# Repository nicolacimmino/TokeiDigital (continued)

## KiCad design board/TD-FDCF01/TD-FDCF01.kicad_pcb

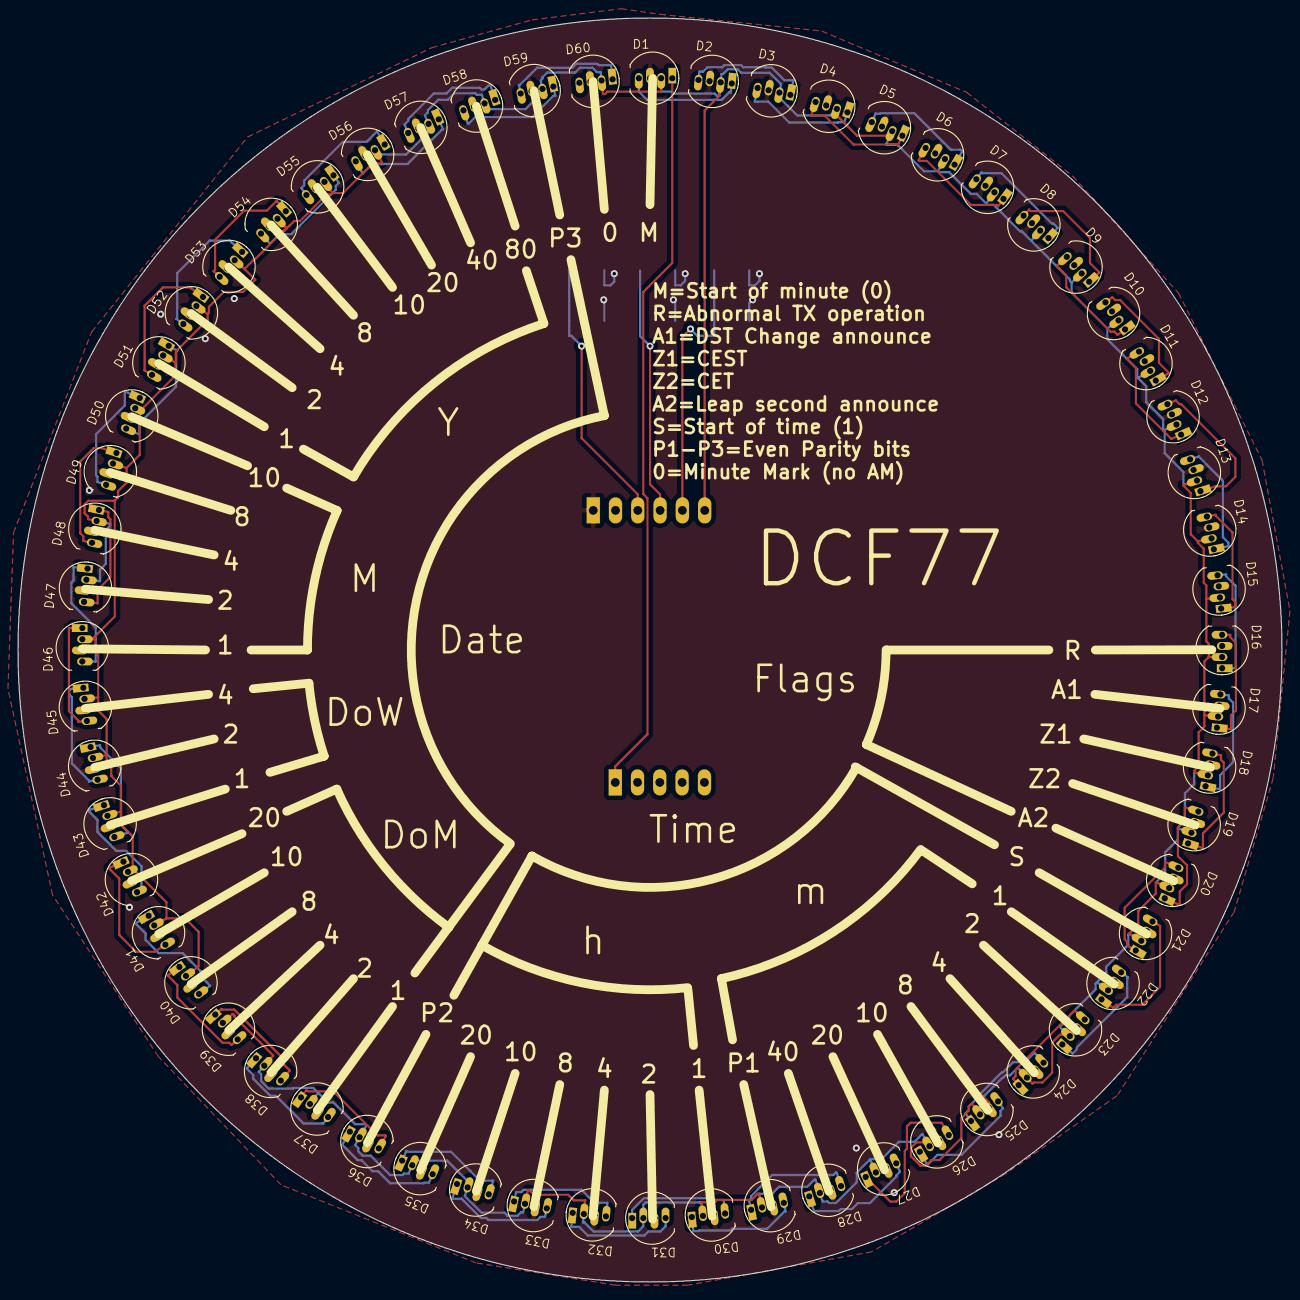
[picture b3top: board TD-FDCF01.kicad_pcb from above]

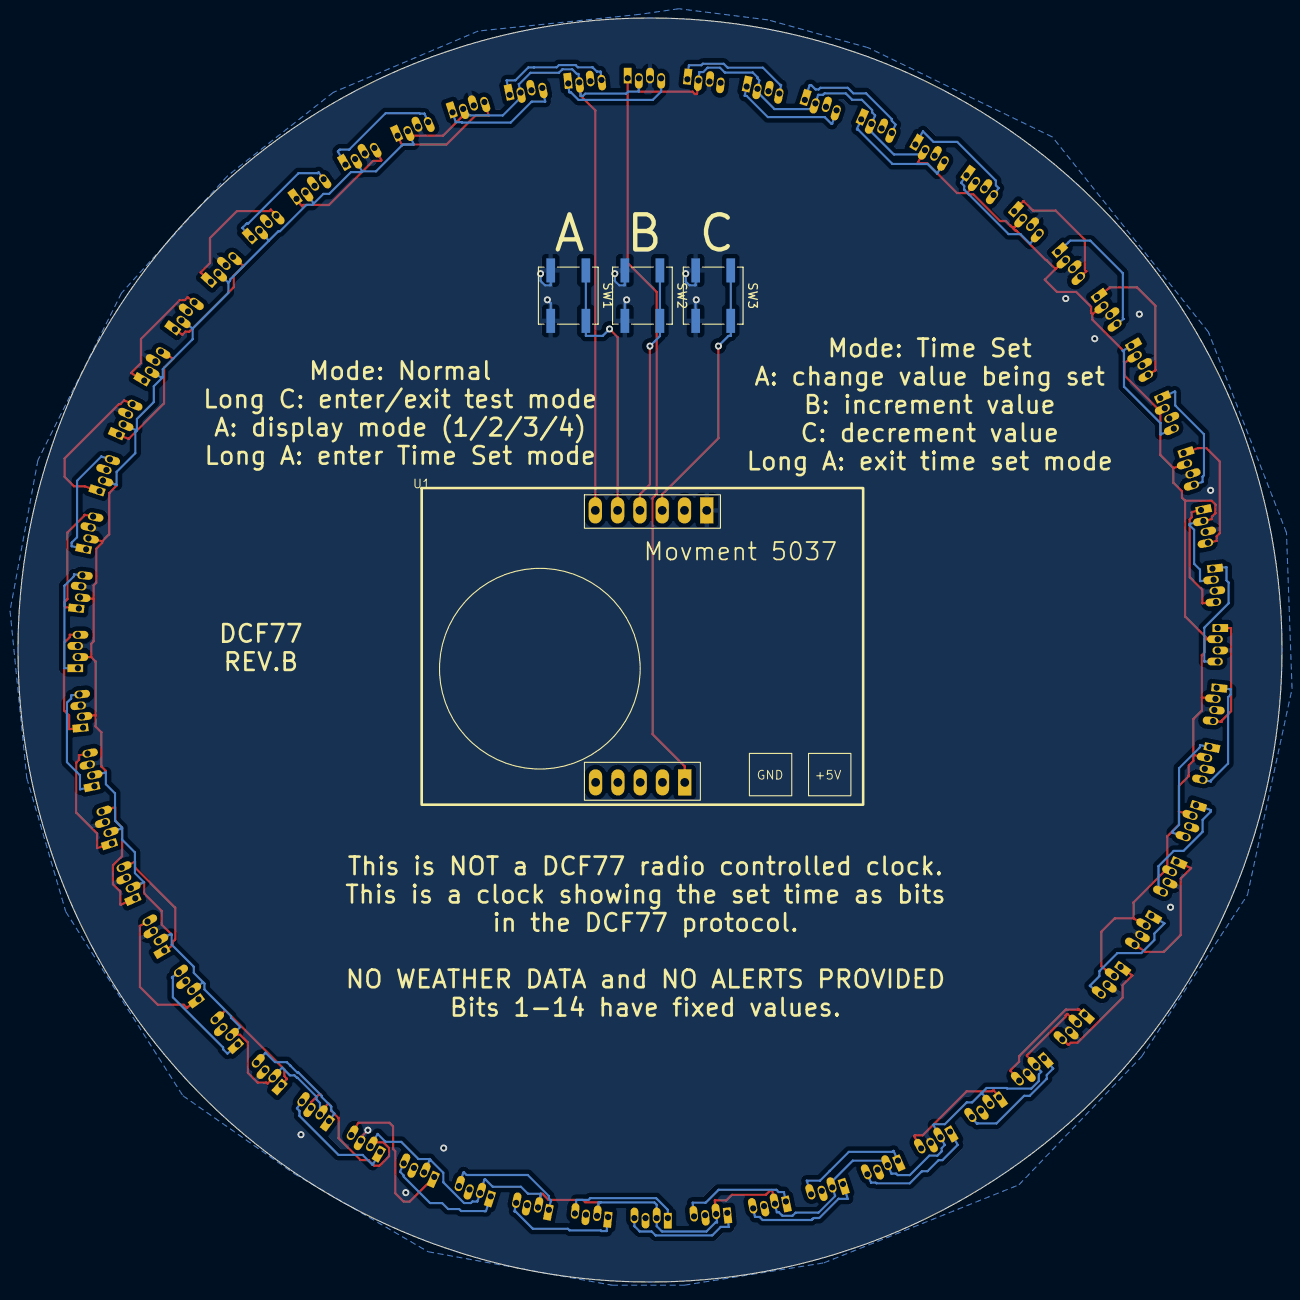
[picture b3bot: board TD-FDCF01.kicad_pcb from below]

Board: 2 copper layers, 144.0 x 144.0 mm, 64 parts (4 on the bottom side), 65 nets.

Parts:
D1, D2, D3, D4, D5, D6, D7, D8, D9, D10, D11, D12, D13, D14, D15, D16, D17, D18, D19, D20, D21, D22, D23, D24, D25, D26, D27, D28, D29, D30, D31, D32, D33, D34, D35, D36, D37, D38, D39, D40, D41, D42, D43, D44, D45, D46, D47, D48, D49, D50, D51, D52, D53, D54, D55, D56, D57, D58, D59, D60: WS2812-5MM
SW1, SW2, SW3: SW_Push; Tactile SW SMD
U1: Movement5037 TH

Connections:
+5V: D1.2 (Vcc), D2.2 (Vcc), D3.2 (Vcc), D4.2 (Vcc), D5.2 (Vcc), D6.2 (Vcc), D7.2 (Vcc), D8.2 (Vcc), D9.2 (Vcc), D10.2 (Vcc), D11.2 (Vcc), D12.2 (Vcc), D13.2 (Vcc), D14.2 (Vcc), D15.2 (Vcc), D16.2 (Vcc), D17.2 (Vcc), D18.2 (Vcc), D19.2 (Vcc), D20.2 (Vcc), D21.2 (Vcc), D22.2 (Vcc), D23.2 (Vcc), D24.2 (Vcc), D25.2 (Vcc), D26.2 (Vcc), D27.2 (Vcc), D28.2 (Vcc), D29.2 (Vcc), D30.2 (Vcc), D31.2 (Vcc), D32.2 (Vcc), D33.2 (Vcc), D34.2 (Vcc), D35.2 (Vcc), D36.2 (Vcc), D37.2 (Vcc), D38.2 (Vcc), D39.2 (Vcc), D40.2 (Vcc), D41.2 (Vcc), D42.2 (Vcc), D43.2 (Vcc), D44.2 (Vcc), D45.2 (Vcc), D46.2 (Vcc), D47.2 (Vcc), D48.2 (Vcc), D49.2 (Vcc), D50.2 (Vcc), D51.2 (Vcc), D52.2 (Vcc), D53.2 (Vcc), D54.2 (Vcc), D55.2 (Vcc), D56.2 (Vcc), D57.2 (Vcc), D58.2 (Vcc), D59.2 (Vcc), D60.2 (Vcc), U1.6 (+5)
/LEDD: D1.1 (DIn), U1.7 (WS2812D)
/LedA/LEDD_CONT: D30.4 (DOut), D31.1 (DIn)
GND: D1.3 (GND), D2.3 (GND), D3.3 (GND), D4.3 (GND), D5.3 (GND), D6.3 (GND), D7.3 (GND), D8.3 (GND), D9.3 (GND), D10.3 (GND), D11.3 (GND), D12.3 (GND), D13.3 (GND), D14.3 (GND), D15.3 (GND), D16.3 (GND), D17.3 (GND), D18.3 (GND), D19.3 (GND), D20.3 (GND), D21.3 (GND), D22.3 (GND), D23.3 (GND), D24.3 (GND), D25.3 (GND), D26.3 (GND), D27.3 (GND), D28.3 (GND), D29.3 (GND), D30.3 (GND), D31.3 (GND), D32.3 (GND), D33.3 (GND), D34.3 (GND), D35.3 (GND), D36.3 (GND), D37.3 (GND), D38.3 (GND), D39.3 (GND), D40.3 (GND), D41.3 (GND), D42.3 (GND), D43.3 (GND), D44.3 (GND), D45.3 (GND), D46.3 (GND), D47.3 (GND), D48.3 (GND), D49.3 (GND), D50.3 (GND), D51.3 (GND), D52.3 (GND), D53.3 (GND), D54.3 (GND), D55.3 (GND), D56.3 (GND), D57.3 (GND), D58.3 (GND), D59.3 (GND), D60.3 (GND), SW1.2, SW2.2, SW3.2, U1.1 (GND)
unnamed: D1.4 (DOut), D2.1 (DIn)
unnamed: D2.4 (DOut), D3.1 (DIn)
unnamed: D3.4 (DOut), D4.1 (DIn)
unnamed: D4.4 (DOut), D5.1 (DIn)
unnamed: D5.4 (DOut), D6.1 (DIn)
unnamed: D6.4 (DOut), D7.1 (DIn)
unnamed: D7.4 (DOut), D8.1 (DIn)
unnamed: D8.4 (DOut), D9.1 (DIn)
unnamed: D9.4 (DOut), D10.1 (DIn)
unnamed: D10.4 (DOut), D11.1 (DIn)
unnamed: D11.4 (DOut), D12.1 (DIn)
unnamed: D12.4 (DOut), D13.1 (DIn)
unnamed: D13.4 (DOut), D14.1 (DIn)
unnamed: D14.4 (DOut), D15.1 (DIn)
unnamed: D15.4 (DOut), D16.1 (DIn)
unnamed: D16.4 (DOut), D17.1 (DIn)
unnamed: D17.4 (DOut), D18.1 (DIn)
unnamed: D18.4 (DOut), D19.1 (DIn)
unnamed: D19.4 (DOut), D20.1 (DIn)
unnamed: D20.4 (DOut), D21.1 (DIn)
unnamed: D21.4 (DOut), D22.1 (DIn)
unnamed: D22.4 (DOut), D23.1 (DIn)
unnamed: D23.4 (DOut), D24.1 (DIn)
unnamed: D24.4 (DOut), D25.1 (DIn)
unnamed: D25.4 (DOut), D26.1 (DIn)
unnamed: D26.4 (DOut), D27.1 (DIn)
unnamed: D27.4 (DOut), D28.1 (DIn)
unnamed: D28.4 (DOut), D29.1 (DIn)
unnamed: D29.4 (DOut), D30.1 (DIn)
unnamed: D31.4 (DOut), D32.1 (DIn)
unnamed: D32.4 (DOut), D33.1 (DIn)
unnamed: D33.4 (DOut), D34.1 (DIn)
unnamed: D34.4 (DOut), D35.1 (DIn)
unnamed: D35.4 (DOut), D36.1 (DIn)
unnamed: D36.4 (DOut), D37.1 (DIn)
unnamed: D37.4 (DOut), D38.1 (DIn)
unnamed: D38.4 (DOut), D39.1 (DIn)
unnamed: D39.4 (DOut), D40.1 (DIn)
unnamed: D40.4 (DOut), D41.1 (DIn)
unnamed: D41.4 (DOut), D42.1 (DIn)
unnamed: D42.4 (DOut), D43.1 (DIn)
unnamed: D43.4 (DOut), D44.1 (DIn)
unnamed: D44.4 (DOut), D45.1 (DIn)
unnamed: D45.4 (DOut), D46.1 (DIn)
unnamed: D46.4 (DOut), D47.1 (DIn)
unnamed: D47.4 (DOut), D48.1 (DIn)
unnamed: D48.4 (DOut), D49.1 (DIn)
unnamed: D49.4 (DOut), D50.1 (DIn)
unnamed: D50.4 (DOut), D51.1 (DIn)
unnamed: D51.4 (DOut), D52.1 (DIn)
unnamed: D52.4 (DOut), D53.1 (DIn)
unnamed: D53.4 (DOut), D54.1 (DIn)
unnamed: D54.4 (DOut), D55.1 (DIn)
unnamed: D55.4 (DOut), D56.1 (DIn)
unnamed: D56.4 (DOut), D57.1 (DIn)
unnamed: D57.4 (DOut), D58.1 (DIn)
unnamed: D58.4 (DOut), D59.1 (DIn)
unnamed: D59.4 (DOut), D60.1 (DIn)
unnamed: SW1.1, U1.5 (BTNA)
unnamed: SW2.1, U1.4 (BTNB)
unnamed: SW3.1, U1.3 (BTNC)

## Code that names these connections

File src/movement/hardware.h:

#ifndef __HARDWARE_H__
#define __HARDWARE_H__

#define BTNA_PIN 0
#define BTNB_PIN 1
#define BTNC_PIN 2

#endif

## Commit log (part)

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2025-01-08 Migrate from other repo
2025-01-16 Rename all projects according to code and remove deps on old libraries
2025-01-16 fix reamdme
2025-01-17 Cleanup 3d prints
2025-01-17 Ignore backup files
2025-01-18 Add WD
2025-01-20 Turn around registers layout
2025-01-20 Cleanup serial interface commands
2025-01-21 More serial IF cleanup
2025-02-08 Add diagnostic heartbeat
2025-02-12 Fix FACE_ID undefined
2025-02-12 Image
2025-02-27 Support tweaks
2025-03-18 Updated Manuals
2025-03-22 Ship with DST off so faces with no date don't act erraticaly on date change unless user sets date with UART
2025-04-29 Ship DCF with DST auto since it has date
2025-04-29 Add DCF manual
2025-04-29 Add different colour palettes for DCF face
2025-04-29 V1 (#2)
    * Add DCF manual
    * Ship DCF with DST auto since it has date
    * Add different colour palettes for DCF face
2025-05-05 Update DCF manual
2025-05-05 Update DCF manual (#3)
2026-02-10 Better makefile, autodiscovery .cpp and build in .build
2026-02-10 New DCF face cover proto
2026-02-13 Face tweaks
2026-02-13 Add editor for DCF77 registers
2026-02-13 Better script with config map
2026-02-20 DCF LEDs radially, tweaks to silkscreen
2026-02-20 Prepare for sale
2026-03-06 Final sale prep
2026-03-20 OET First steps
2026-03-27 Final default color map
2026-05-22 OET schematic
